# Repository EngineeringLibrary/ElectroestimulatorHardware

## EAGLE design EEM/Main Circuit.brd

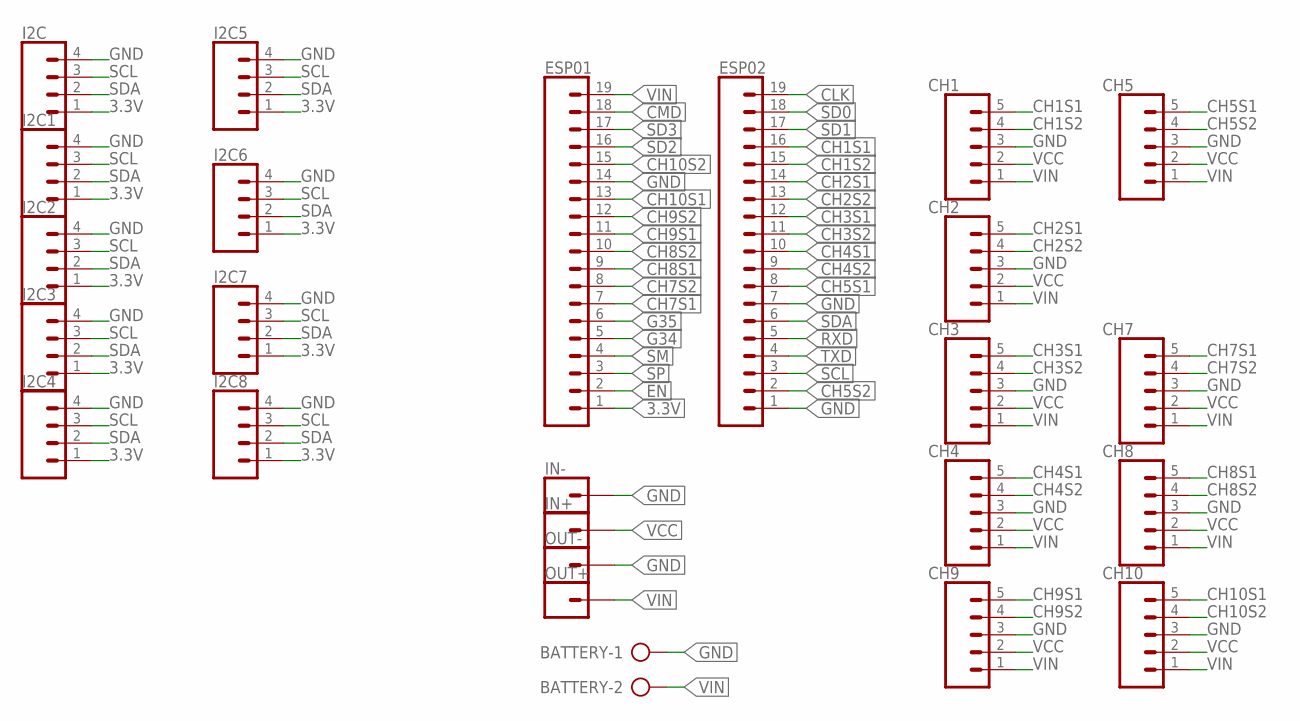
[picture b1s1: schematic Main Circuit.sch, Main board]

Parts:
BATTERY: AK500/2-H
CH1, CH2, CH3, CH4, CH5, CH7, CH8, CH9, CH10: CONN_05; 1X05
ESP01, ESP02: CONN_19; 1X19
I2C, I2C1, I2C2, I2C3, I2C4, I2C5, I2C6, I2C7, I2C8: CONN_04; 1X04
IN+: CONN_01; 1X01
IN-: CONN_01; 1X01
OUT+: CONN_01; 1X01
OUT-: CONN_01; 1X01

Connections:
3.3V: ESP01.1, I2C.1, I2C1.1, I2C2.1, I2C3.1, I2C4.1, I2C5.1, I2C6.1, I2C7.1, I2C8.1
CH1S1: CH1.5, ESP02.16
CH1S2: CH1.4, ESP02.15
CH2S1: CH2.5, ESP02.14
CH2S2: CH2.4, ESP02.13
CH3S1: CH3.5, ESP02.12
CH3S2: CH3.4, ESP02.11
CH4S1: CH4.5, ESP02.10
CH4S2: CH4.4, ESP02.9
CH5S1: CH5.5, ESP02.8
CH5S2: CH5.4, ESP02.2
CH7S1: CH7.5, ESP01.7
CH7S2: CH7.4, ESP01.8
CH8S1: CH8.5, ESP01.9
CH8S2: CH8.4, ESP01.10
CH9S1: CH9.5, ESP01.11
CH9S2: CH9.4, ESP01.12
CH10S1: CH10.5, ESP01.13
CH10S2: CH10.4, ESP01.15
CLK: ESP02.19
CMD: ESP01.18
EN: ESP01.2
G34: ESP01.5
G35: ESP01.6
GND: BATTERY.1, CH1.3, CH2.3, CH3.3, CH4.3, CH5.3, CH7.3, CH8.3, CH9.3, CH10.3, ESP01.14, ESP02.1, ESP02.7, I2C.4, I2C1.4, I2C2.4, I2C3.4, I2C4.4, I2C5.4, I2C6.4, I2C7.4, I2C8.4, IN-.1, OUT-.1
RXD: ESP02.5
SCL: ESP02.3, I2C.3, I2C1.3, I2C2.3, I2C3.3, I2C4.3, I2C5.3, I2C6.3, I2C7.3, I2C8.3
SD0: ESP02.18
SD1: ESP02.17
SD2: ESP01.16
SD3: ESP01.17
SDA: ESP02.6, I2C.2, I2C1.2, I2C2.2, I2C3.2, I2C4.2, I2C5.2, I2C6.2, I2C7.2, I2C8.2
SM: ESP01.4
SP: ESP01.3
TXD: ESP02.4
VCC: CH1.2, CH2.2, CH3.2, CH4.2, CH5.2, CH7.2, CH8.2, CH9.2, CH10.2, IN+.1
VIN: BATTERY.2, CH1.1, CH2.1, CH3.1, CH4.1, CH5.1, CH7.1, CH8.1, CH9.1, CH10.1, ESP01.19, OUT+.1

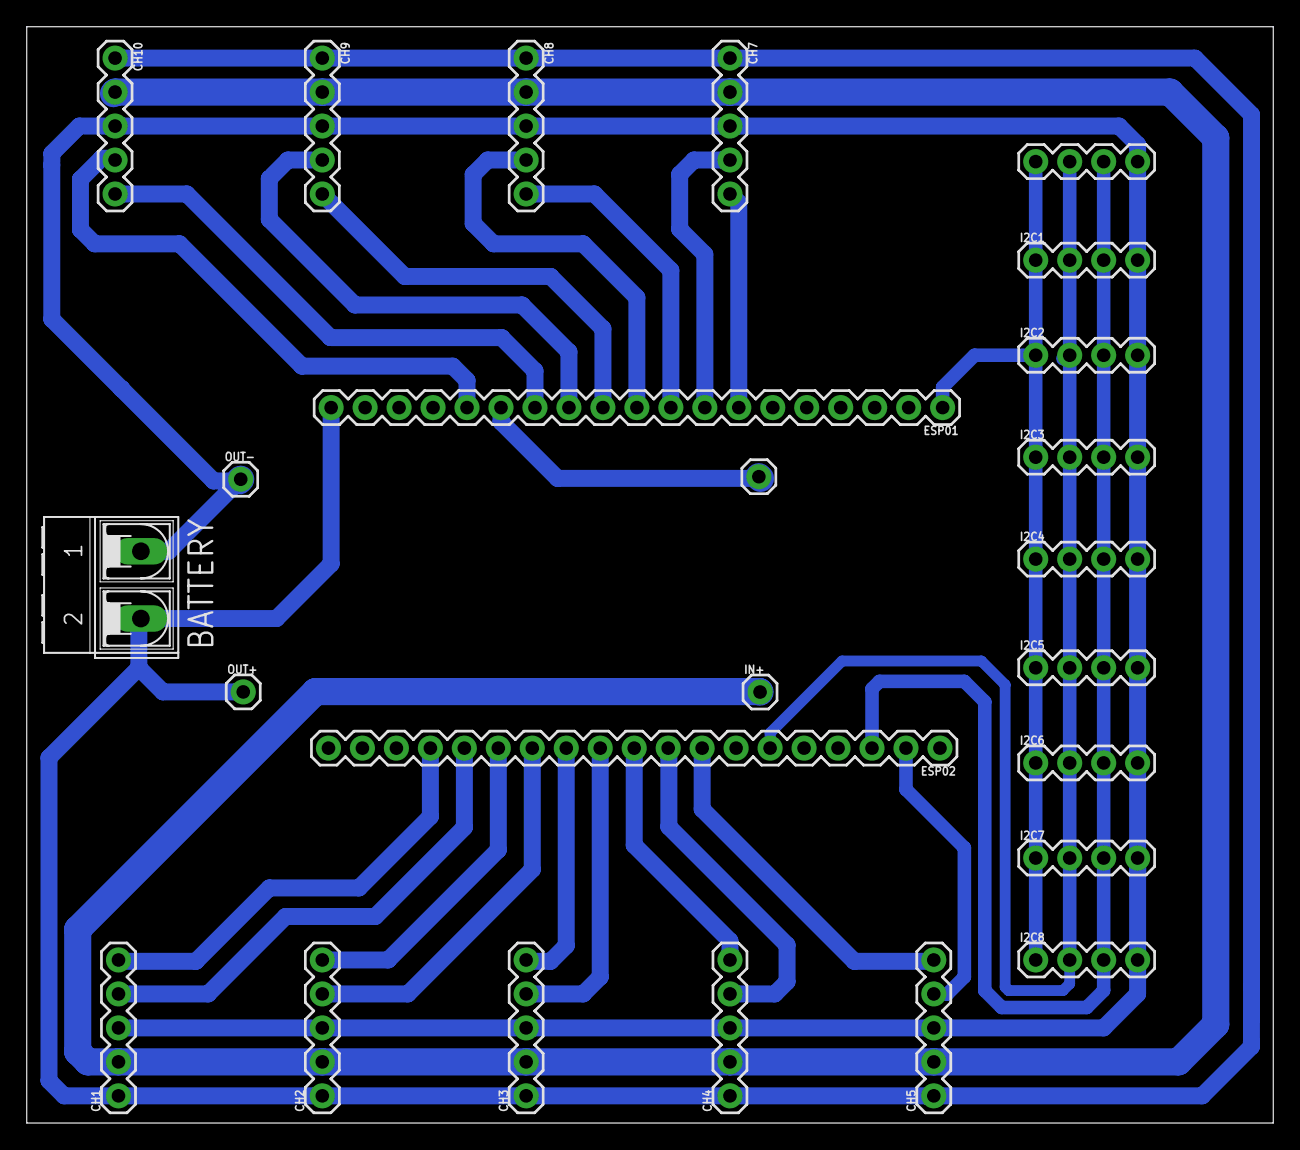
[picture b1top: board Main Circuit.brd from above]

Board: 2 copper layers, 93.2 x 82.0 mm, 25 parts (0 on the bottom side), 24 nets.

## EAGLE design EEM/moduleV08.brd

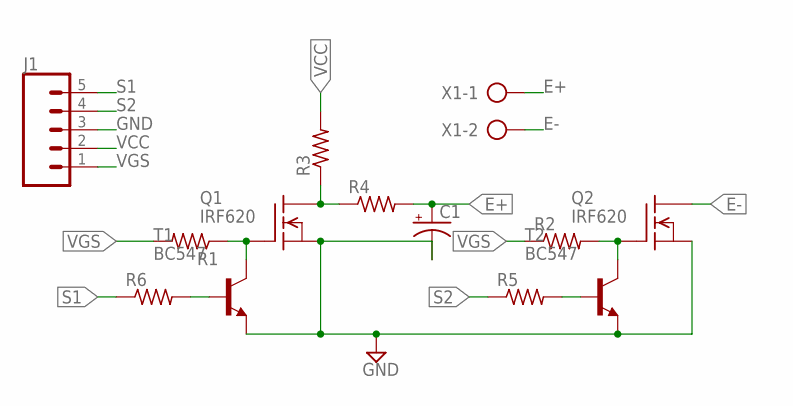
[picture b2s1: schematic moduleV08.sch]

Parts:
C1: CAPACITOR-PE3.5-8; E3,5-8
J1: CONN_05; 1X05
Q1, Q2: IRF620; TO220
R1, R2, R3, R4, R5, R6: R-US_0204/7; 0204/7
T1, T2: BC547; TO92
X1: AK500/2-H

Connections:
E+: C1.+, R4.2, X1.1
E-: Q2.2 (D), X1.2
GND: C1.-, J1.3, Q1.3 (S), Q2.3 (S), T1.1 (E), T2.1 (E)
unnamed: Q1.1 (G), R1.1, T1.3 (C)
unnamed: R6.2, T1.2 (B)
unnamed: Q1.2 (D), R3.1, R4.1
unnamed: R5.2, T2.2 (B)
unnamed: Q2.1 (G), R2.2, T2.3 (C)
S1: J1.5, R6.1
S2: J1.4, R5.1
VCC: J1.2, R3.2
VGS: J1.1, R1.2, R2.1

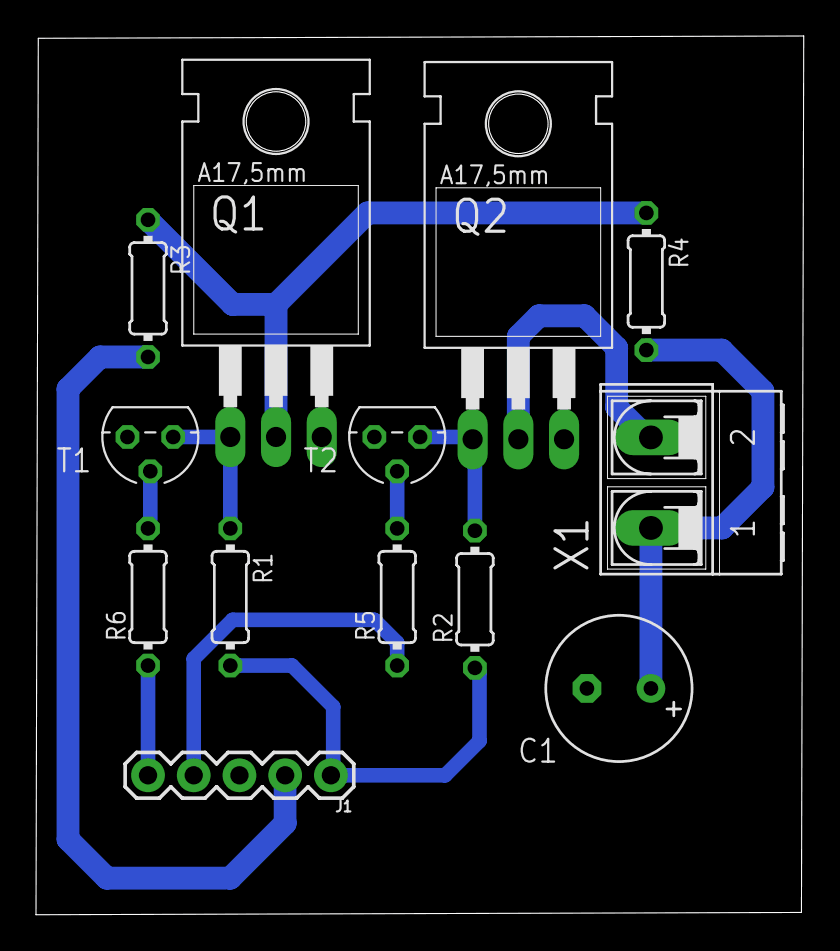
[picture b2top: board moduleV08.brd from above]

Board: 2 copper layers, 42.7 x 48.8 mm, 13 parts (0 on the bottom side), 12 nets.

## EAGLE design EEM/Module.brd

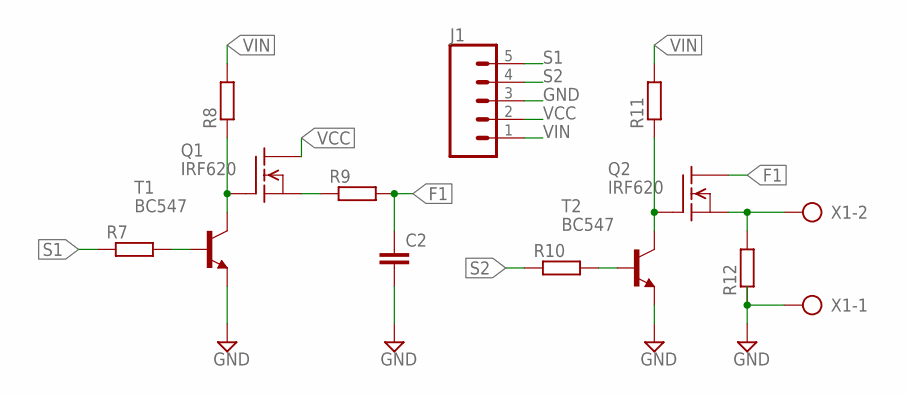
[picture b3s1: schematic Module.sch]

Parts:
C2: C5/5; C5B5
J1: CONN_05; 1X05
Q1, Q2: IRF620; TO220
R7, R8, R9, R10, R11, R12: R-EU_0309/12; 0309/12
T1, T2: BC547; TO92
X1: AK500/2-H

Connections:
F1: C2.1, Q2.2 (D), R9.2
GND: C2.2, J1.3, R12.1, T1.1 (E), T2.1 (E), X1.1
unnamed: Q1.1 (G), R8.1, T1.3 (C)
unnamed: Q2.1 (G), R11.1, T2.3 (C)
unnamed: R7.2, T1.2 (B)
unnamed: R10.2, T2.2 (B)
unnamed: Q1.3 (S), R9.1
unnamed: Q2.3 (S), R12.2, X1.2
S1: J1.5, R7.1
S2: J1.4, R10.1
VCC: J1.2, Q1.2 (D)
VIN: J1.1, R8.2, R11.2

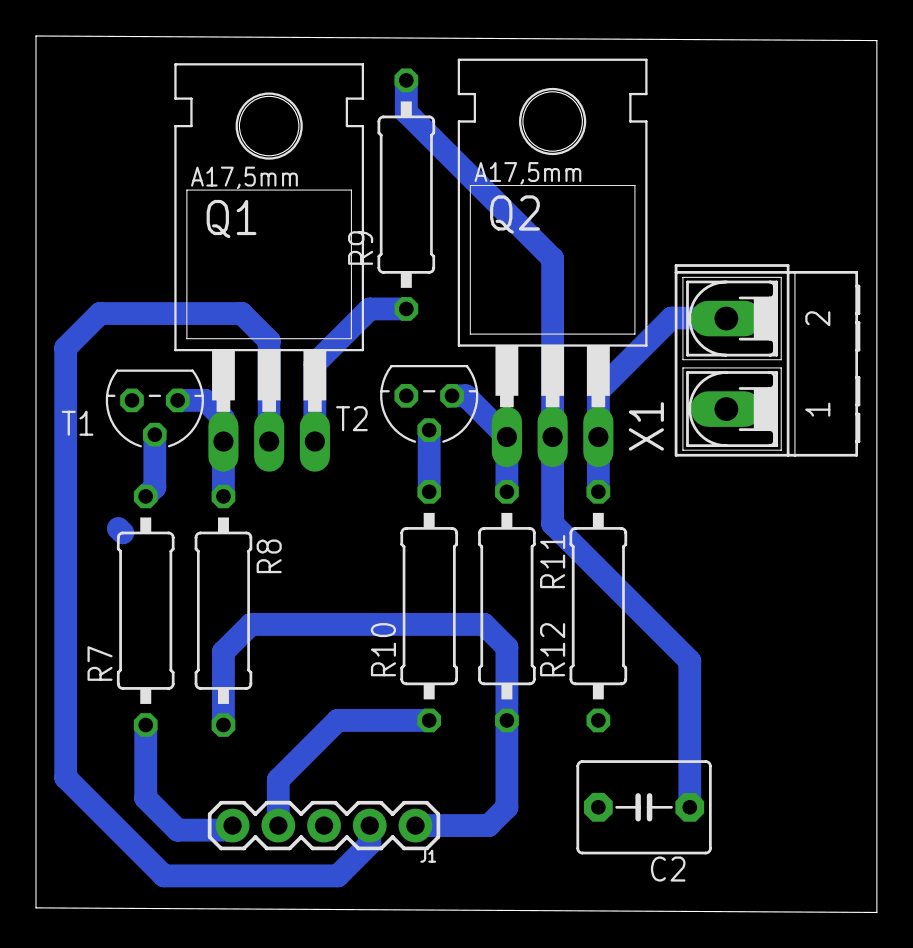
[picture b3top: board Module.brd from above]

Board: 2 copper layers, 46.7 x 48.7 mm, 13 parts (0 on the bottom side), 12 nets.

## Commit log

2019-07-18 First version of Electroestimulator Hardware
2019-07-25 Alteração feita para correção de chaveamento no Low Side e adição de componentes SMD
2019-10-04 Esquemático do teste 02/10/19

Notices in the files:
parts and their libraries:
SparkFun-Connectors: Licensing: Creative Commons ShareAlike 4.0 International - https://creativecommons.org/licenses/by-sa/4.0
